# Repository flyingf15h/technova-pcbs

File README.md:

# TechNova PCBs

KiCad 9 source files and schematics for the TechNova hacker badge and star clip.

## Planet badge

- CH32V203 RISC-V microcontroller
- 1.3" 128x64 OLED and a 4-button d-pad
- 9 WS2812B-2020 addressable LEDs
- NFC tag (NT3H2111) with an on-board coil, so you can tap it with a phone
- USB-C charging for a 3.7 V LiPo (TP4056), with a power slide switch
- SWD test pads on the back for programming
- 81.4 x 60 mm, 2 layers, purple mask with ENIG gold art

Files are in `technova-badge/`, schematic PDF is `technova-badge/technova_badge-schematic.pdf`.

## Star clip

- Orion drawn in 7 red 0603 LEDs
- ATtiny202, programmed over UPDI
- One button for modes and soft power off
- Runs off a CR1220 coin cell
- 41 x 39 mm, 2 layers, blue mask with ENIG gold art

Files are in `star-clip/`, schematic PDF is `star-clip/star_clip-schematic.pdf`.

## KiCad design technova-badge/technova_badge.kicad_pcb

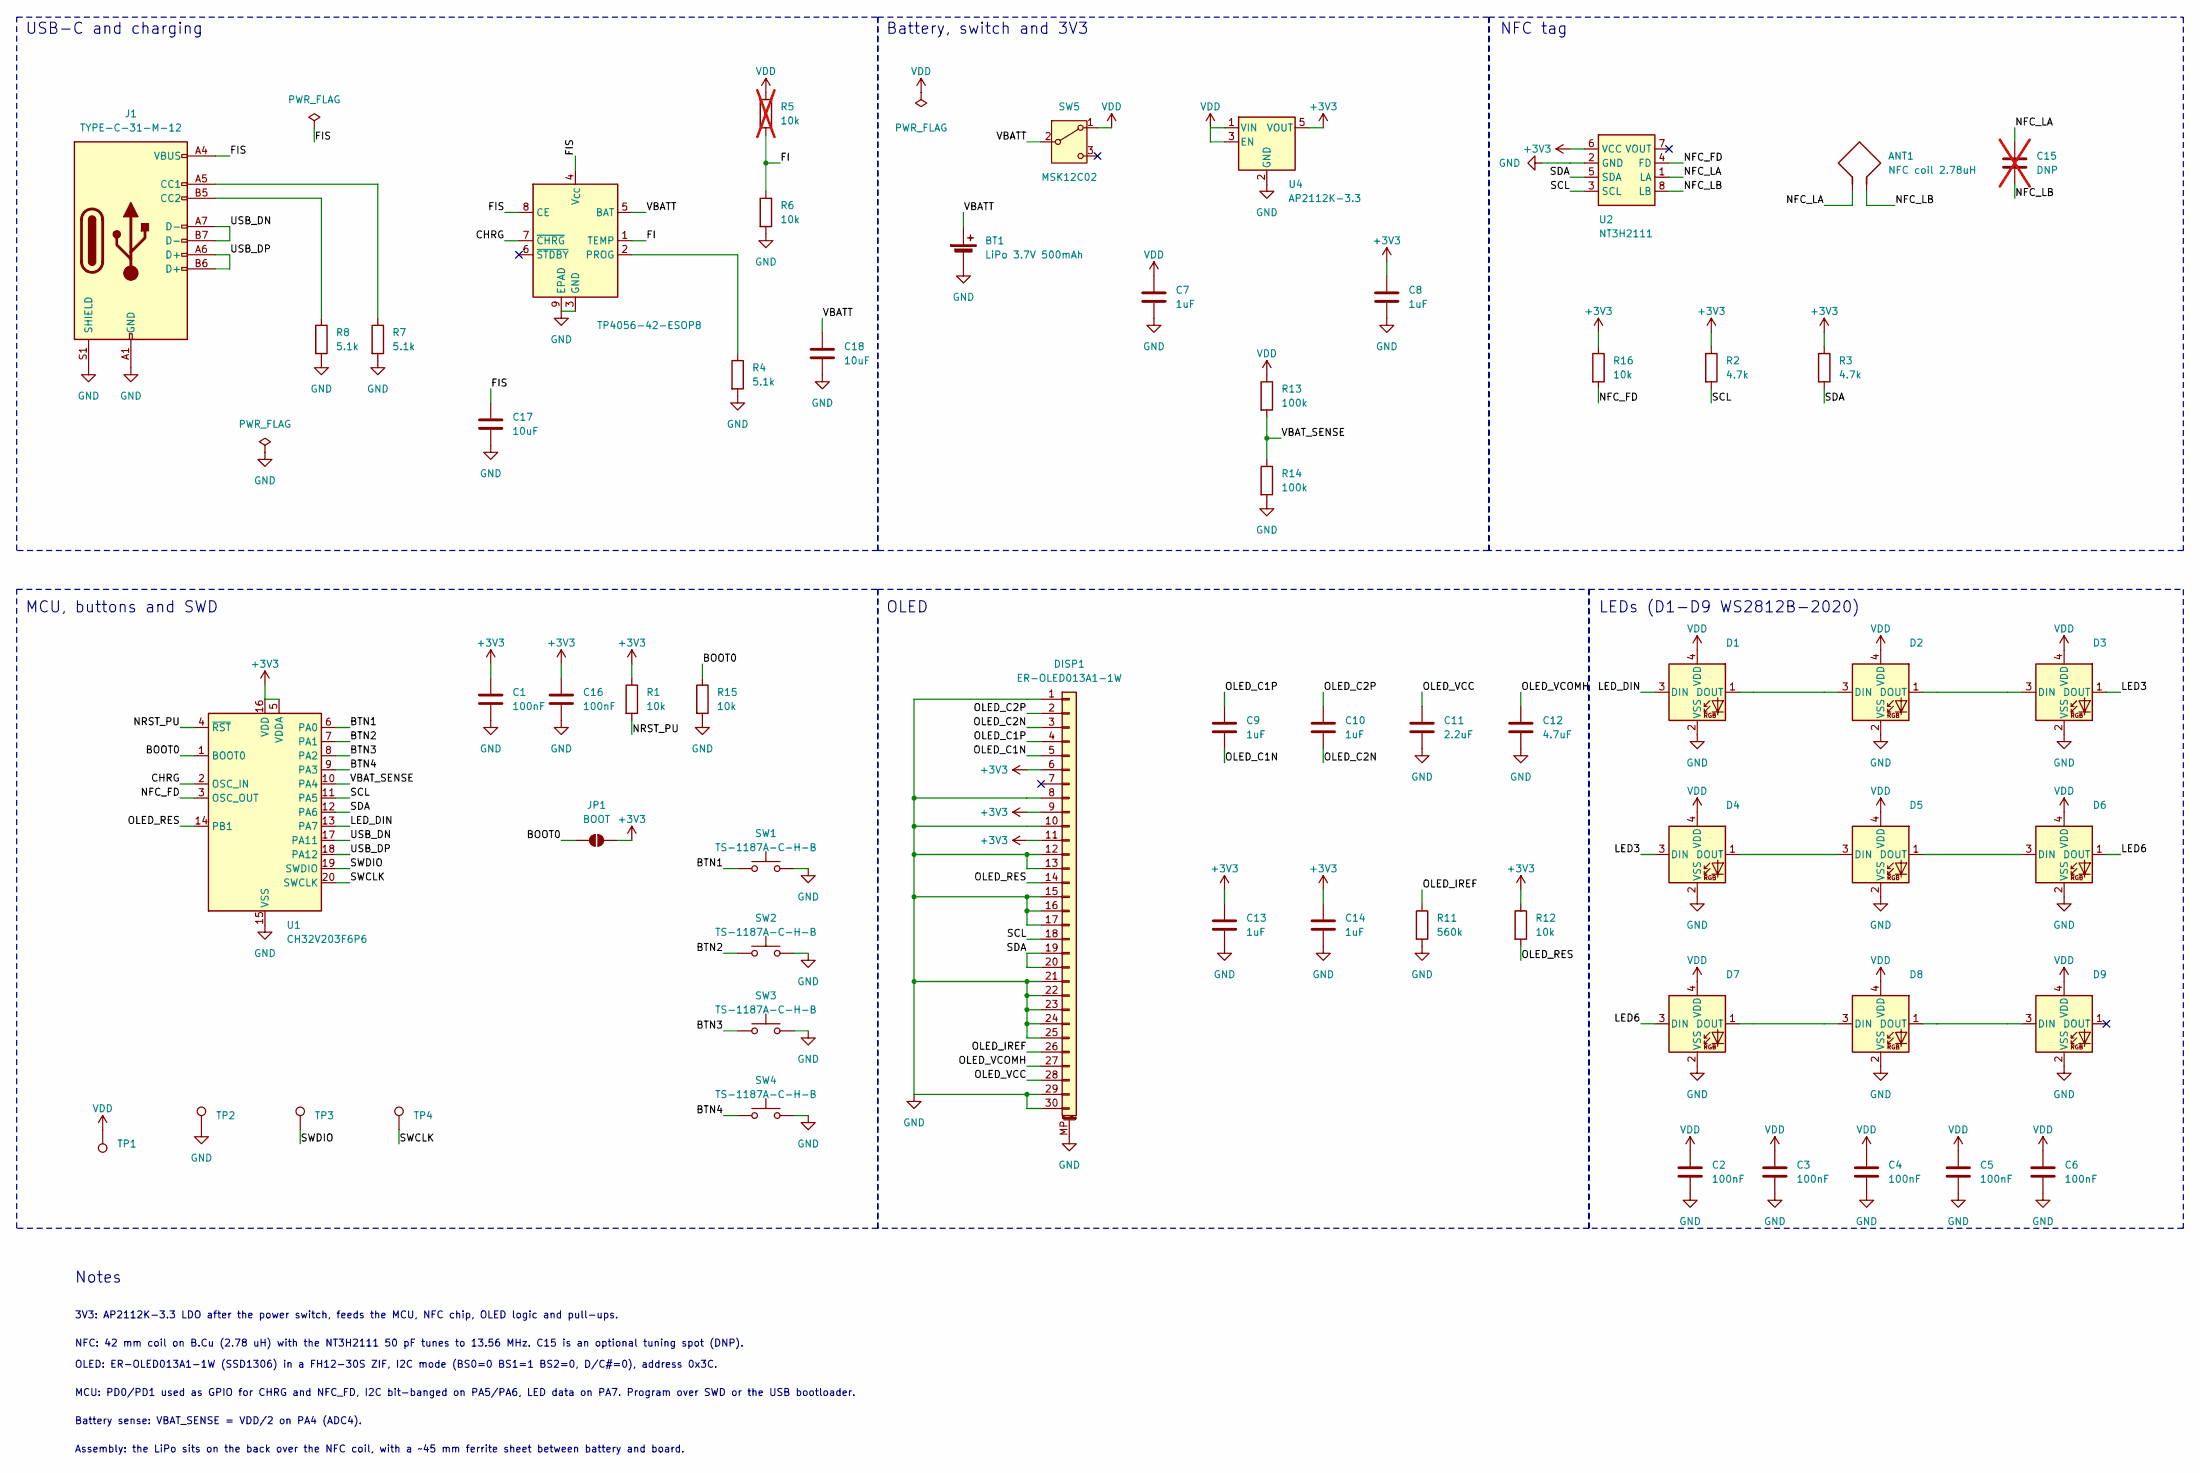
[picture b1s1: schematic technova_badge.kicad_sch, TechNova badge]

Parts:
ANT1: NFC coil 2.78uH; NFC_Coil_Spiral_D42mm_6T
BT1: LiPo 3.7V 500mAh; JST_PH_B2B-PH-K_1x02_P2.00mm_Vertical; LCSC C131337
C1, C2, C3, C4, C5, C6, C16: 100nF; C_0402_1005Metric; LCSC C1525
C7, C8, C9, C10, C13, C14: 1uF; C_0402_1005Metric; LCSC C52923
C11: 2.2uF; C_0402_1005Metric; LCSC C12530
C12: 4.7uF; C_0402_1005Metric; LCSC C23733
C15: DNP; C_0402_1005Metric; LCSC C1548; not fitted
C17, C18: 10uF; C_0603_1608Metric; LCSC C19702
D1, D2, D3, D4, D5, D6, D7, D8, D9: WS2812B-2020-V6; LED_WS2812B-2020_PLCC4_2.0x2.0mm; LCSC C52917434
DISP1: ER-OLED013A1-1W; FPC-SMD_30P-P0.50_XUNPU_FPC-05F-30PH20; LCSC C2856808
J1: TYPE-C-31-M-12; USB_C_Receptacle_HRO_TYPE-C-31-M-12; LCSC C165948
JP1: BOOT; SolderJumper-2_P1.3mm_Open_RoundedPad1.0x1.5mm
R1, R6, R12, R15, R16: 10k; R_0402_1005Metric; LCSC C25744
R2, R3: 4.7k; R_0402_1005Metric; LCSC C25900
R4, R7, R8: 5.1k; R_0402_1005Metric; LCSC C25905
R5: 10k; R_0402_1005Metric; LCSC C25744; not fitted
R11: 560k; R_0402_1005Metric; LCSC C132339
R13, R14: 100k; R_0402_1005Metric; LCSC C25741
SW1, SW2, SW3, SW4: TS-1187A-C-H-B; SW_Push_1P1T_XKB_TS-1187A; LCSC C528025
SW5: MSK12C02; SW_SPDT_Shouhan_MSK12C02; LCSC C431540
TP1: TP_VDD; TestPoint_Pad_D1.5mm
TP2: TP_GND; TestPoint_Pad_D1.5mm
TP3: TP_SWDIO; TestPoint_Pad_D1.5mm
TP4: TP_SWCLK; TestPoint_Pad_D1.5mm
U1: CH32V203F6P6; TSSOP-20_4.4x6.5mm_P0.65mm; LCSC C3040880
U2: NT3H2111; XQFN-8_L1.6-W1.6-P0.50-BL_NT3H2111W0FHKH; LCSC C710403
U3: TP4056-42-ESOP8; SOIC-8-1EP_3.9x4.9mm_P1.27mm_EP2.41x3.3mm; LCSC C16581
U4: AP2112K-3.3; SOT-23-5; LCSC C51118

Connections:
+3V3: C1.1, C8.1, C13.1, C14.1, C16.1, DISP1.6, DISP1.9, DISP1.11, JP1.2 (B), R1.1, R2.1, R3.1, R12.1, R16.1, U1.5 (PA1), U1.16 (PC6), U2.6 (VCC), U4.5 (VOUT)
/BOOT0: JP1.1 (A), R15.1, U1.1 (PD4)
/BTN1: SW1.1, U1.6 (PA2)
/BTN2: SW2.1, U1.7 (VSS)
/BTN3: SW3.1, U1.8 (PD0)
/BTN4: SW4.1, U1.9 (VDD)
/CHRG: U1.2 (PD5), U3.7 (~CHRG)
/FI: R5.1, R6.1, U3.1 (TEMP)
/FIS: C17.1, J1.A4 (VBUS), J1.A9 (VBUS), J1.B4 (VBUS), J1.B9 (VBUS), U3.4 (V_{CC}), U3.8 (CE)
/LED3: D3.1 (DOUT), D4.3 (DIN)
/LED6: D6.1 (DOUT), D7.3 (DIN)
/LED_DIN: D1.3 (DIN), U1.13 (PC3)
/NFC_FD: R16.2, U1.3 (PD6), U2.4 (FD)
/NFC_LA: ANT1.1, C15.1, U2.1 (LA)
/NFC_LB: ANT1.2, C15.2, U2.8 (LB)
/NRST_PU: R1.2, U1.4 (PD7)
/OLED_C1N: C9.2, DISP1.5
/OLED_C1P: C9.1, DISP1.4
/OLED_C2N: C10.2, DISP1.3
/OLED_C2P: C10.1, DISP1.2
/OLED_IREF: DISP1.26, R11.1
/OLED_RES: DISP1.14, R12.2, U1.14 (PC4)
/OLED_VCC: C11.1, DISP1.28
/OLED_VCOMH: C12.1, DISP1.27
/SCL: DISP1.18, R2.2, U1.11 (PC1), U2.3 (SCL)
/SDA: DISP1.19, DISP1.20, R3.2, U1.12 (PC2), U2.5 (SDA)
/SWCLK: TP4.1, U1.20 (PD3)
/SWDIO: TP3.1, U1.19 (PD2)
/USB_DN: J1.A7 (D-), J1.B7 (D-), U1.17 (PC7)
/USB_DP: J1.A6 (D+), J1.B6 (D+), U1.18 (PD1)
/VBATT: BT1.1 (+), C18.1, SW5.2 (B), U3.5 (BAT)
/VBAT_SENSE: R13.2, R14.1, U1.10 (PC0)
GND: BT1.2 (-), C1.2, C2.2, C3.2, C4.2, C5.2, C6.2, C7.2, C8.2, C11.2, C12.2, C13.2, C14.2, C16.2, C17.2, C18.2, D1.2 (VSS), D2.2 (VSS), D3.2 (VSS), D4.2 (VSS), D5.2 (VSS), D6.2 (VSS), D7.2 (VSS), D8.2 (VSS), D9.2 (VSS), DISP1.1, DISP1.8, DISP1.10, DISP1.12, DISP1.13, DISP1.15, DISP1.16, DISP1.17, DISP1.21, DISP1.22, DISP1.23, DISP1.24, DISP1.25, DISP1.29, DISP1.30, DISP1.MP (MountPin), J1.A1 (GND), J1.A12 (GND), J1.B1 (GND), J1.B12 (GND), J1.S1 (SHIELD), R4.2, R6.2, R7.2, R8.2, R11.2, R14.2, R15.2, SW1.2, SW2.2, SW3.2, SW4.2, TP2.1, U1.15 (PC5), U2.2 (GND), U3.3 (GND), U3.9 (EPAD), U4.2 (GND)
unnamed: D1.1 (DOUT), D2.3 (DIN)
unnamed: D2.1 (DOUT), D3.3 (DIN)
unnamed: D4.1 (DOUT), D5.3 (DIN)
unnamed: D5.1 (DOUT), D6.3 (DIN)
unnamed: D7.1 (DOUT), D8.3 (DIN)
unnamed: D8.1 (DOUT), D9.3 (DIN)
unnamed: J1.A5 (CC1), R7.1
unnamed: J1.B5 (CC2), R8.1
unnamed: R4.1, U3.2 (PROG)
VDD: C2.1, C3.1, C4.1, C5.1, C6.1, C7.1, D1.4 (VDD), D2.4 (VDD), D3.4 (VDD), D4.4 (VDD), D5.4 (VDD), D6.4 (VDD), D7.4 (VDD), D8.4 (VDD), D9.4 (VDD), R5.2, R13.1, SW5.1 (A), TP1.1, U4.1 (VIN), U4.3 (EN)

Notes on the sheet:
Notes
3V3: AP2112K-3.3 LDO after the power switch, feeds the MCU, NFC chip, OLED logic and pull-ups.
NFC: 42 mm coil on B.Cu (2.78 uH) with the NT3H2111 50 pF tunes to 13.56 MHz. C15 is an optional tuning spot (DNP).
OLED: ER-OLED013A1-1W (SSD1306) in a FH12-30S ZIF, I2C mode (BS0=0 BS1=1 BS2=0, D/C#=0), address 0x3C.
MCU: PD0/PD1 used as GPIO for CHRG and NFC_FD, I2C bit-banged on PA5/PA6, LED data on PA7. Program over SWD or the USB bootloader.
Battery sense: VBAT_SENSE = VDD/2 on PA4 (ADC4).
Assembly: the LiPo sits on the back over the NFC coil, with a ~45 mm ferrite sheet between battery and board.
USB-C and charging
Battery, switch and 3V3
NFC tag
MCU, buttons and SWD
OLED
LEDs (D1-D9 WS2812B-2020)

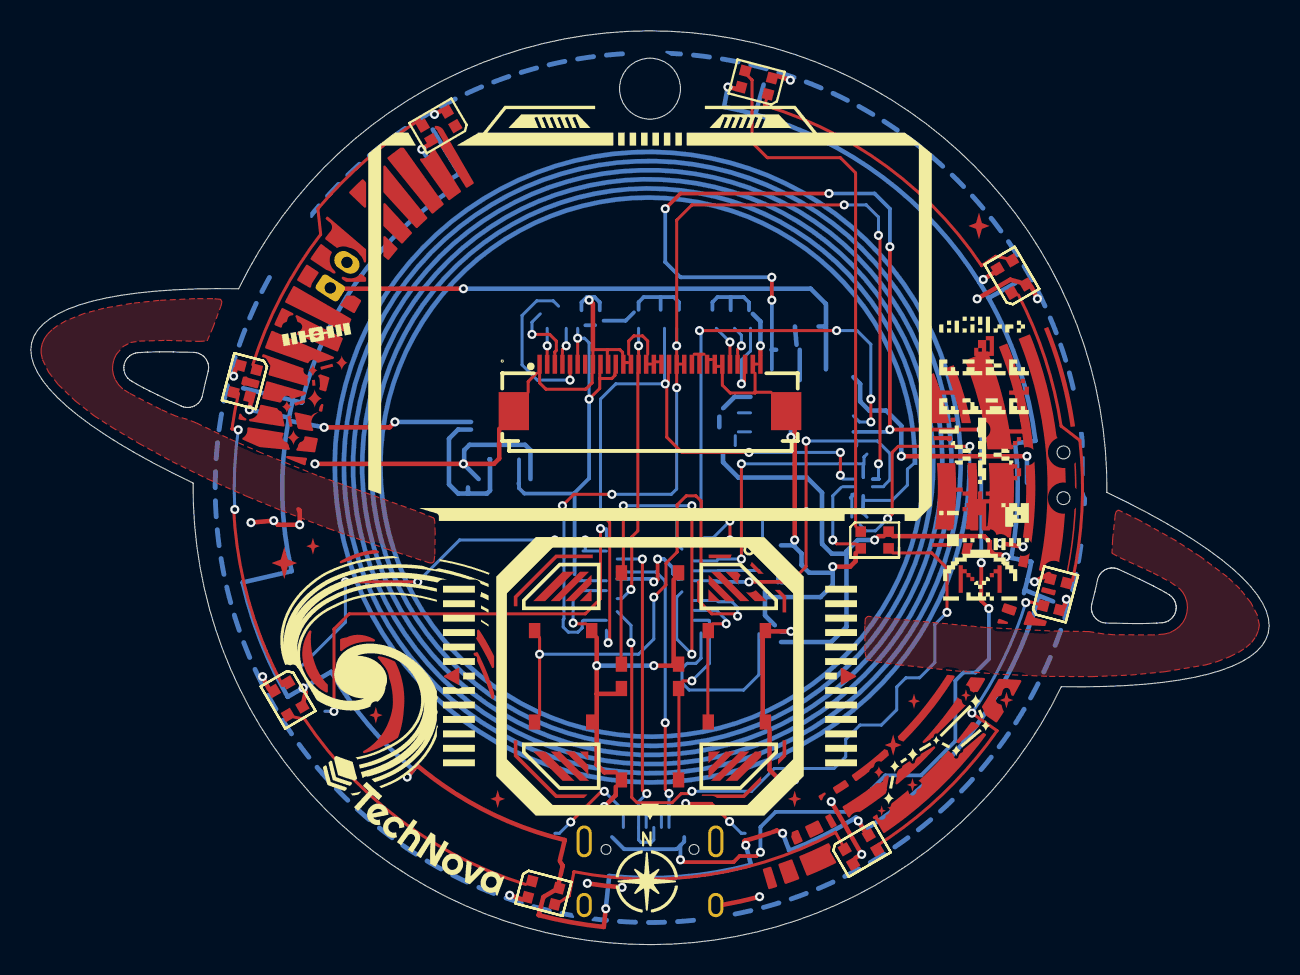
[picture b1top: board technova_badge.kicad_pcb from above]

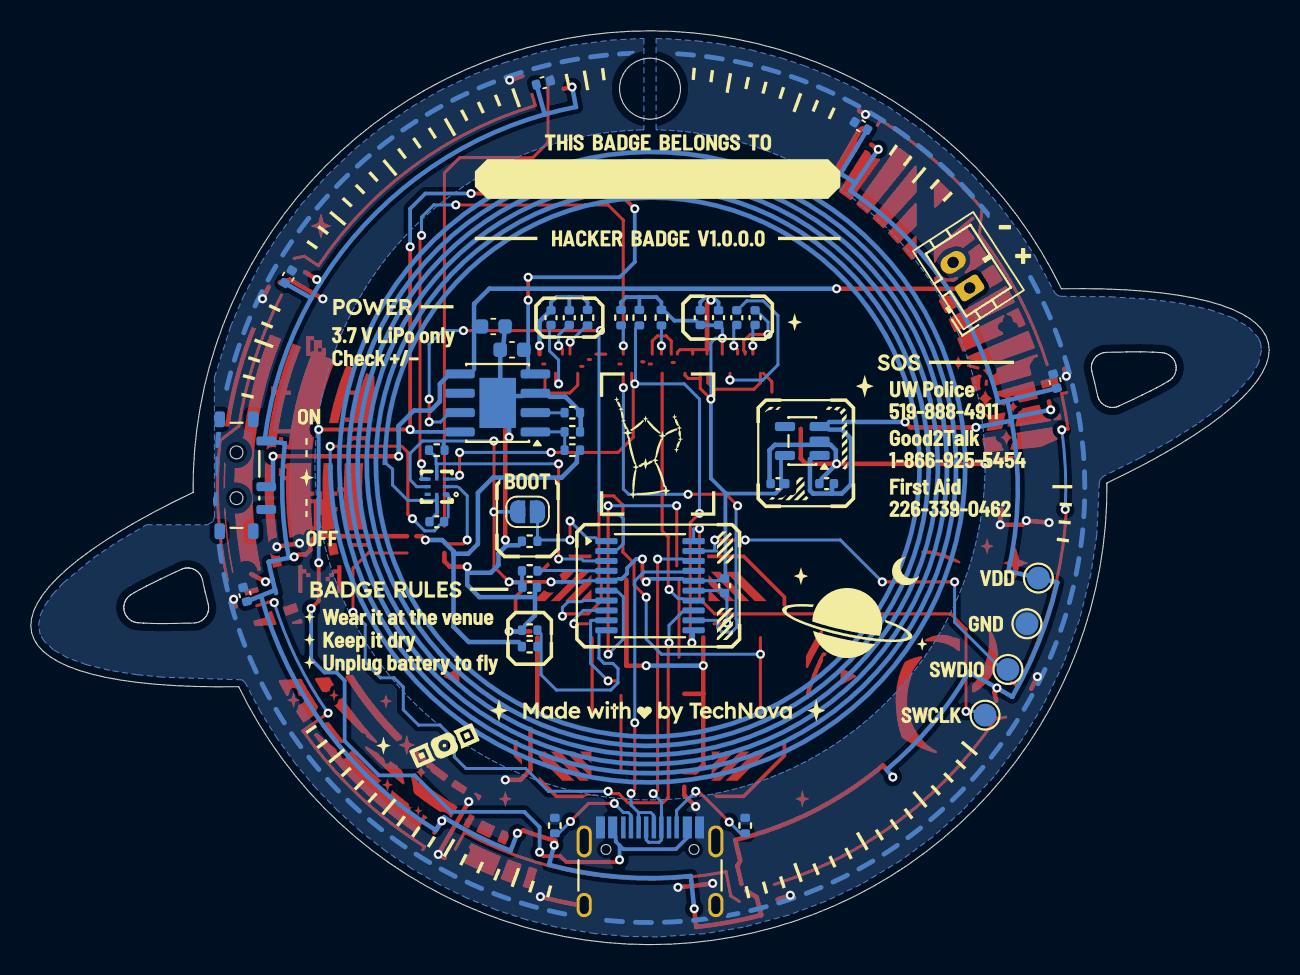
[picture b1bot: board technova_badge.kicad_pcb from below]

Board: 2 copper layers, 81.3 x 60.0 mm, 59 parts (45 on the bottom side), 43 nets.

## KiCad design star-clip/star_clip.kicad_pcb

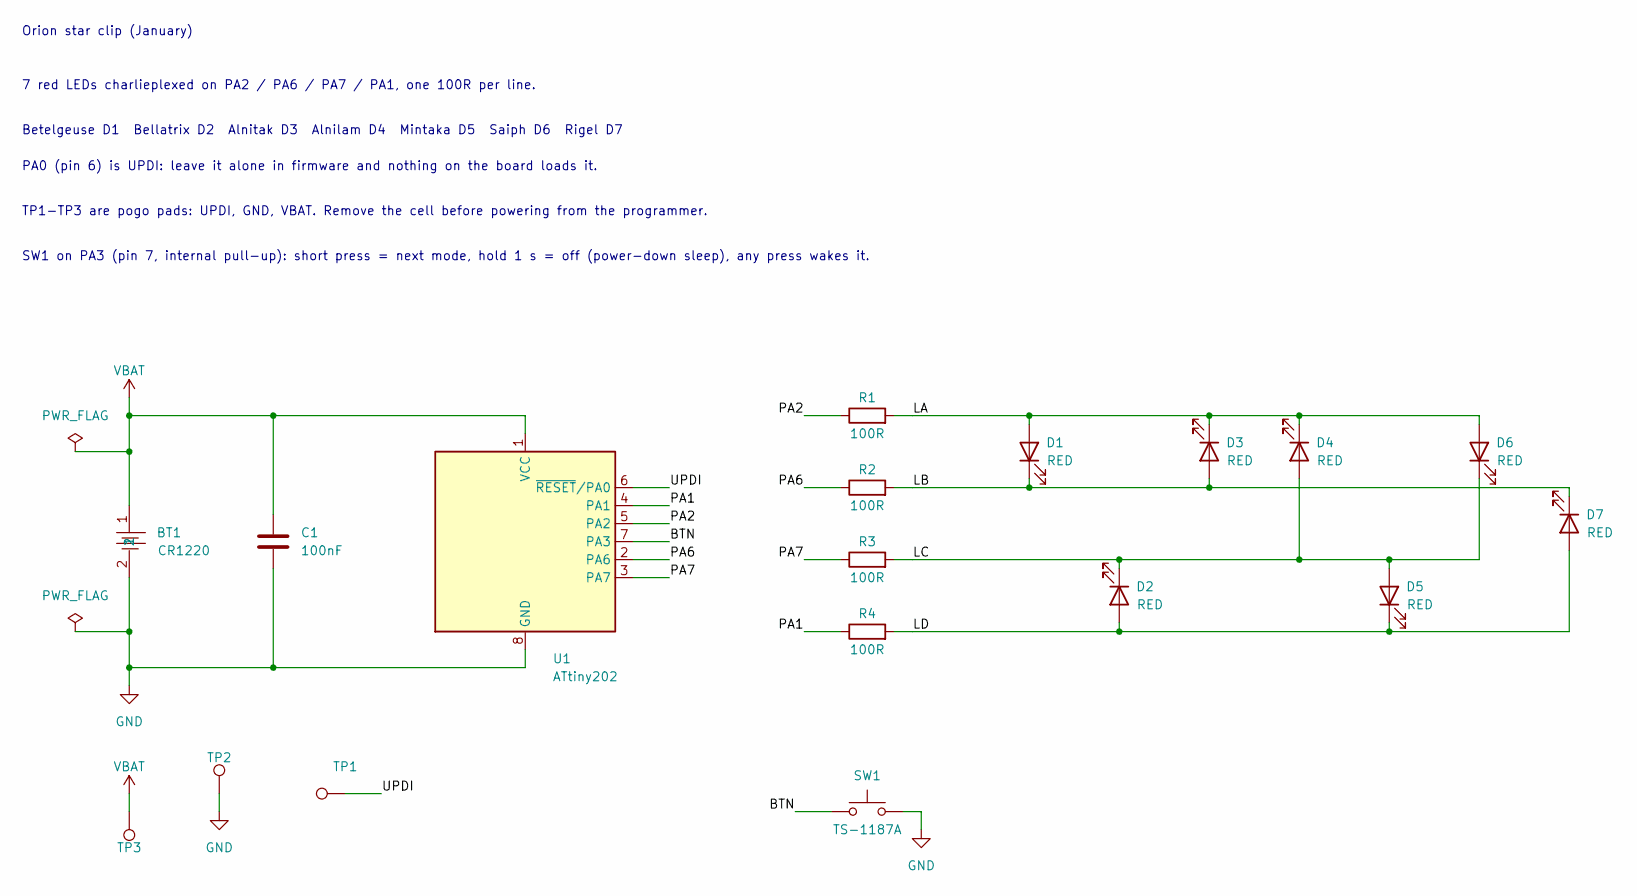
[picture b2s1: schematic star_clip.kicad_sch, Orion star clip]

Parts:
BT1: CR1220; BAT-SMD_CR1220-2ZX; LCSC C7498147
C1: 100nF; C_0402_1005Metric; LCSC C1525
D1, D2, D3, D4, D5, D6, D7: RED; LED_0603_1608Metric; LCSC C2286
R1, R2, R3, R4: 100R; R_0402_1005Metric; LCSC C106232
SW1: TS-1187A; SW_Push_1P1T_XKB_TS-1187A; LCSC C528025
TP1: UPDI; TestPoint_Pad_D1.5mm
TP2: GND; TestPoint_Pad_D1.5mm
TP3: VBAT; TestPoint_Pad_D1.5mm
U1: ATtiny202; SOIC-8_3.9x4.9mm_P1.27mm; LCSC C2052951

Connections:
/BTN: SW1.1, U1.7 (PA3)
/LA: D1.2 (A), D3.1 (K), D4.1 (K), D6.2 (A), R1.2
/LB: D1.1 (K), D3.2 (A), D7.1 (K), R2.2
/LC: D2.1 (K), D4.2 (A), D5.2 (A), D6.1 (K), R3.2
/LD: D2.2 (A), D5.1 (K), D7.2 (A), R4.2
/PA1: R4.1, U1.4 (PA1)
/PA2: R1.1, U1.5 (PA2)
/PA6: R2.1, U1.2 (PA6)
/PA7: R3.1, U1.3 (PA7)
/UPDI: TP1.1, U1.6 (~RESET/PA0)
GND: BT1.2, C1.2, SW1.2, TP2.1, U1.8 (GND)
VBAT: BT1.1, C1.1, TP3.1, U1.1 (VCC)

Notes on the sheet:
Orion star clip (January)
7 red LEDs charlieplexed on PA2 / PA6 / PA7 / PA1, one 100R per line.
Betelgeuse D1 Bellatrix D2 Alnitak D3 Alnilam D4 Mintaka D5 Saiph D6 Rigel D7
PA0 (pin 6) is UPDI: leave it alone in firmware and nothing on the board loads it.
SW1 on PA3 (pin 7, internal pull-up): short press = next mode, hold 1 s = off (power-down sleep), any press wakes it.
TP1-TP3 are pogo pads: UPDI, GND, VBAT. Remove the cell before powering from the programmer.

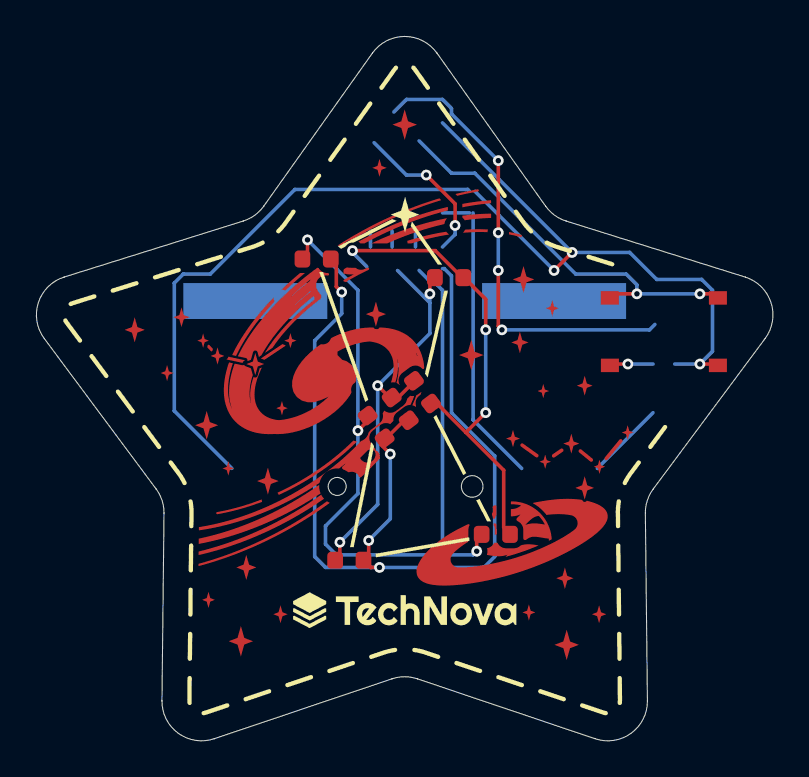
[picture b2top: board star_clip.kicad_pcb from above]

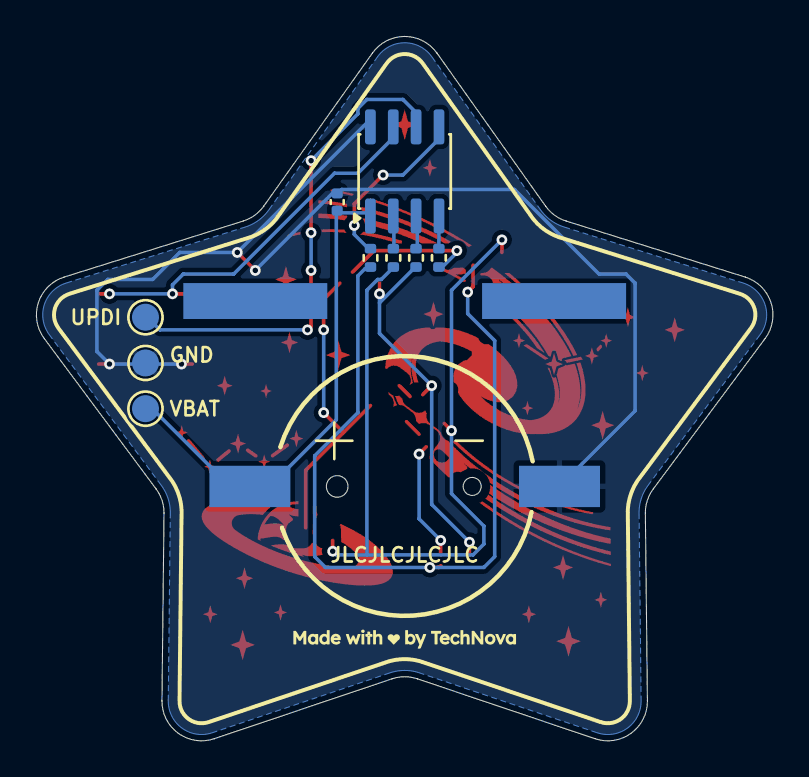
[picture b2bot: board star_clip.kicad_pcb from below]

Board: 2 copper layers, 40.9 x 39.1 mm, 18 parts (10 on the bottom side), 12 nets.
